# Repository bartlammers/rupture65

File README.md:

# Rupture65, a split 65% keyboard

## Left

[Project](./Left)  
[iBom](http://htmlpreview.github.io/?https://github.com/bartlammers/rupture65/blob/master/Left/bom/ibom.html)

## Right

[Project](./Right)  
[iBom](http://htmlpreview.github.io/?https://github.com/bartlammers/rupture65/blob/master/Right/bom/ibom.html)

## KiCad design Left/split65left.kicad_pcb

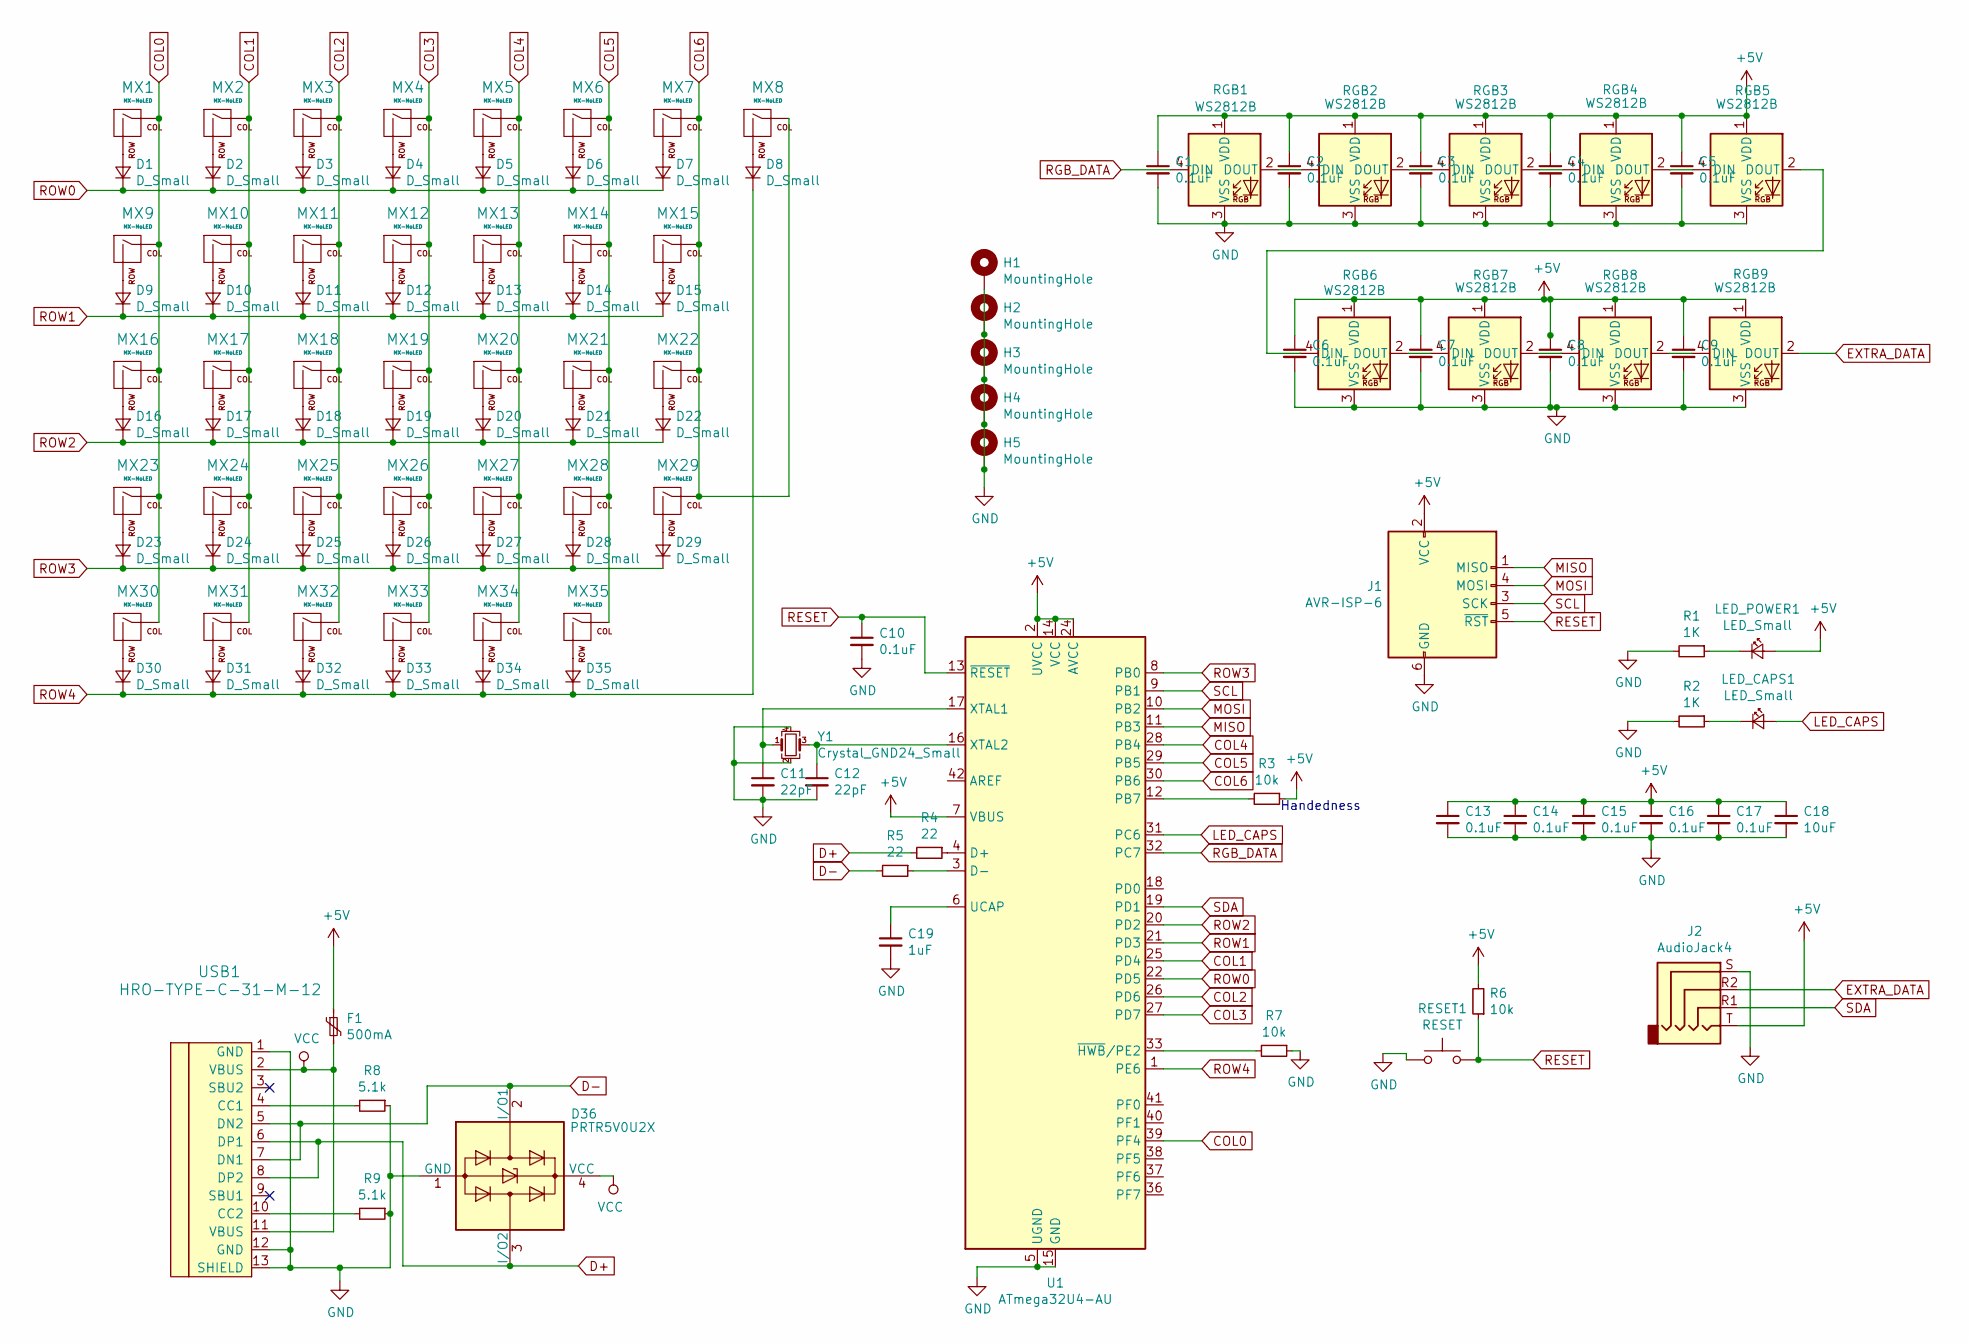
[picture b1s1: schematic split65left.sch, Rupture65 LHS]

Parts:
C1, C2, C3, C4, C5, C6, C7, C8, C9, C10, C13, C14, C15, C16, C17: 0.1uF; C_0805_2012Metric_Pad1.15x1.40mm_HandSolder
C11, C12: 22pF; C_0805_2012Metric_Pad1.15x1.40mm_HandSolder
C18: 10uF; C_0805_2012Metric_Pad1.15x1.40mm_HandSolder
C19: 1uF; C_0805_2012Metric_Pad1.15x1.40mm_HandSolder
D1, D2, D3, D4, D5, D6, D7, D8, D9, D10, D11, D12, D13, D14, D15, D16, D17, D18, D19, D20, D21, D22, D23, D24, D25, D26, D27, D28, D29, D30, D31, D32, D33, D34, D35: D_Small; D_SOD123_hand
D36: PRTR5V0U2X; SOT-143
F1: 500mA; Fuse_1206_3216Metric_Pad1.42x1.75mm_HandSolder
H1, H2, H3, H4, H5: MountingHole; MountingHole_2.2mm_M2_Pad_Via
J1: AVR-ISP-6; PinHeader_2x03_P2.54mm_Vertical
J2: AudioJack4; PJ-3200B-4A
LED_CAPS1: LED_Small; LED_0805_2012Metric
LED_POWER1: LED_Small; LED_0805_2012Metric
MX1, MX2, MX3, MX4, MX5, MX6, MX7, MX8, MX9, MX11, MX12, MX13, MX14, MX15, MX16, MX18, MX19, MX20, MX21, MX22, MX23, MX25, MX26, MX27, MX28, MX29, MX30: MX-NoLED; SW_Cherry_MX_1.00u_PCB
MX10: MX-NoLED; SW_Cherry_MX_1.50u_PCB
MX17: MX-NoLED; SW_Cherry_MX_1.75u_PCB
MX24: MX-NoLED; SW_Cherry_MX_2.25u_PCB
MX31, MX32, MX33, MX35: MX-NoLED; SW_Cherry_MX_1.25u_PCB
MX34: MX-NoLED; SW_Cherry_MX_2.25u_PCB_flippedstab
R1, R2: 1K; R_0805_2012Metric_Pad1.15x1.40mm_HandSolder
R3, R6, R7: 10k; R_0805_2012Metric_Pad1.15x1.40mm_HandSolder
R4, R5: 22; R_0805_2012Metric_Pad1.15x1.40mm_HandSolder
R8, R9: 5.1k; R_0805_2012Metric_Pad1.15x1.40mm_HandSolder
RESET1: RESET; SW_SPST_SKQG_WithStem
RGB1, RGB2, RGB3, RGB4, RGB5, RGB6, RGB7, RGB8, RGB9: WS2812B; LED_WS2812B_PLCC4_5.0x5.0mm_P3.2mm
U1: ATmega32U4-AU; TQFP-44_10x10mm_P0.8mm
USB1: HRO-TYPE-C-31-M-12; HRO-TYPE-C-31-M-12-HandSoldering
Y1: Crystal_GND24_Small; Crystal_SMD_3225-4Pin_3.2x2.5mm

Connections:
+5V: C1.1, C2.1, C3.1, C4.1, C5.1, C6.1, C7.1, C8.1, C9.1, C13.1, C14.1, C15.1, C16.1, C17.1, C18.1, F1.1, J1.2 (VCC), J2.T, LED_POWER1.2 (A), R3.1, R6.2, RGB1.1 (VDD), RGB2.1 (VDD), RGB3.1 (VDD), RGB4.1 (VDD), RGB5.1 (VDD), RGB6.1 (VDD), RGB7.1 (VDD), RGB8.1 (VDD), RGB9.1 (VDD), U1.2 (UVCC), U1.7 (VBUS), U1.14 (VCC), U1.24 (AVCC), U1.34 (VCC), U1.44 (AVCC)
COL0: MX1.1 (COL), MX9.1 (COL), MX16.1 (COL), MX23.1 (COL), MX30.1 (COL), U1.39 (PF4)
COL1: MX2.1 (COL), MX10.1 (COL), MX17.1 (COL), MX24.1 (COL), MX31.1 (COL), U1.25 (PD4)
COL2: MX3.1 (COL), MX11.1 (COL), MX18.1 (COL), MX25.1 (COL), MX32.1 (COL), U1.26 (PD6)
COL3: MX4.1 (COL), MX12.1 (COL), MX19.1 (COL), MX26.1 (COL), MX33.1 (COL), U1.27 (PD7)
COL4: MX5.1 (COL), MX13.1 (COL), MX20.1 (COL), MX27.1 (COL), MX34.1 (COL), U1.28 (PB4)
COL5: MX6.1 (COL), MX14.1 (COL), MX21.1 (COL), MX28.1 (COL), MX35.1 (COL), U1.29 (PB5)
COL6: MX7.1 (COL), MX8.1 (COL), MX15.1 (COL), MX22.1 (COL), MX29.1 (COL), U1.30 (PB6)
D+: D36.3 (I/O2), R4.2, USB1.6 (DP1), USB1.8 (DP2)
D-: D36.2 (I/O1), R5.2, USB1.5 (DN2), USB1.7 (DN1)
EXTRA_DATA: J2.R2, RGB9.2 (DOUT)
GND: C1.2, C2.2, C3.2, C4.2, C5.2, C6.2, C7.2, C8.2, C9.2, C10.2, C11.2, C12.2, C13.2, C14.2, C15.2, C16.2, C17.2, C18.2, C19.2, D36.1 (GND), H1.1, H2.1, H3.1, H4.1, H5.1, J1.6 (GND), J2.S, R1.2, R2.2, R7.1, R8.1, R9.1, RESET1.1, RGB1.3 (VSS), RGB2.3 (VSS), RGB3.3 (VSS), RGB4.3 (VSS), RGB5.3 (VSS), RGB6.3 (VSS), RGB7.3 (VSS), RGB8.3 (VSS), RGB9.3 (VSS), U1.5 (UGND), U1.15 (GND), U1.23 (GND), U1.35 (GND), U1.43 (GND), USB1.1 (GND), USB1.12 (GND), USB1.13 (SHIELD), Y1.2, Y1.4
LED_CAPS: LED_CAPS1.2 (A), U1.31 (PC6)
MISO: J1.1 (MISO), U1.11 (PB3)
MOSI: J1.4 (MOSI), U1.10 (PB2)
unnamed: C11.1, U1.17 (XTAL1), Y1.1
unnamed: C12.1, U1.16 (XTAL2), Y1.3
unnamed: C19.1, U1.6 (UCAP)
unnamed: D1.2 (A), MX1.2 (ROW)
unnamed: D2.2 (A), MX2.2 (ROW)
unnamed: D3.2 (A), MX3.2 (ROW)
unnamed: D4.2 (A), MX4.2 (ROW)
unnamed: D5.2 (A), MX5.2 (ROW)
unnamed: D6.2 (A), MX6.2 (ROW)
unnamed: D7.2 (A), MX7.2 (ROW)
unnamed: D8.2 (A), MX8.2 (ROW)
unnamed: D9.2 (A), MX9.2 (ROW)
unnamed: D10.2 (A), MX10.2 (ROW)
unnamed: D11.2 (A), MX11.2 (ROW)
unnamed: D12.2 (A), MX12.2 (ROW)
unnamed: D13.2 (A), MX13.2 (ROW)
unnamed: D14.2 (A), MX14.2 (ROW)
unnamed: D15.2 (A), MX15.2 (ROW)
unnamed: D16.2 (A), MX16.2 (ROW)
unnamed: D17.2 (A), MX17.2 (ROW)
unnamed: D18.2 (A), MX18.2 (ROW)
unnamed: D19.2 (A), MX19.2 (ROW)
unnamed: D20.2 (A), MX20.2 (ROW)
unnamed: D21.2 (A), MX21.2 (ROW)
unnamed: D22.2 (A), MX22.2 (ROW)
unnamed: D23.2 (A), MX23.2 (ROW)
unnamed: D24.2 (A), MX24.2 (ROW)
unnamed: D25.2 (A), MX25.2 (ROW)
unnamed: D26.2 (A), MX26.2 (ROW)
unnamed: D27.2 (A), MX27.2 (ROW)
unnamed: D28.2 (A), MX28.2 (ROW)
unnamed: D29.2 (A), MX29.2 (ROW)
unnamed: D30.2 (A), MX30.2 (ROW)
unnamed: D31.2 (A), MX31.2 (ROW)
unnamed: D32.2 (A), MX32.2 (ROW)
unnamed: D33.2 (A), MX33.2 (ROW)
unnamed: D34.2 (A), MX34.2 (ROW)
unnamed: D35.2 (A), MX35.2 (ROW)
unnamed: LED_CAPS1.1 (K), R2.1
unnamed: LED_POWER1.1 (K), R1.1
unnamed: R3.2, U1.12 (PB7)
unnamed: R4.1, U1.4 (D+)
unnamed: R5.1, U1.3 (D-)
unnamed: R7.2, U1.33 (~HWB~/PE2)
unnamed: R8.2, USB1.4 (CC1)
unnamed: R9.2, USB1.10 (CC2)
unnamed: RGB1.2 (DOUT), RGB2.4 (DIN)
unnamed: RGB2.2 (DOUT), RGB3.4 (DIN)
unnamed: RGB3.2 (DOUT), RGB4.4 (DIN)
unnamed: RGB4.2 (DOUT), RGB5.4 (DIN)
unnamed: RGB5.2 (DOUT), RGB6.4 (DIN)
unnamed: RGB6.2 (DOUT), RGB7.4 (DIN)
unnamed: RGB7.2 (DOUT), RGB8.4 (DIN)
unnamed: RGB8.2 (DOUT), RGB9.4 (DIN)
RESET: C10.1, J1.5 (~RST), R6.1, RESET1.2, U1.13 (~RESET)
RGB_DATA: RGB1.4 (DIN), U1.32 (PC7)
ROW0: D1.1 (K), D2.1 (K), D3.1 (K), D4.1 (K), D5.1 (K), D6.1 (K), D7.1 (K), U1.22 (PD5)
ROW1: D9.1 (K), D10.1 (K), D11.1 (K), D12.1 (K), D13.1 (K), D14.1 (K), D15.1 (K), U1.21 (PD3)
ROW2: D16.1 (K), D17.1 (K), D18.1 (K), D19.1 (K), D20.1 (K), D21.1 (K), D22.1 (K), U1.20 (PD2)
ROW3: D23.1 (K), D24.1 (K), D25.1 (K), D26.1 (K), D27.1 (K), D28.1 (K), D29.1 (K), U1.8 (PB0)
ROW4: D8.1 (K), D30.1 (K), D31.1 (K), D32.1 (K), D33.1 (K), D34.1 (K), D35.1 (K), U1.1 (PE6)
SCL: J1.3 (SCK), U1.9 (PB1)
SDA: J2.R1, U1.19 (PD1)
VCC: D36.4 (VCC), F1.2, USB1.2 (VBUS), USB1.11 (VBUS)

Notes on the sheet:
Handedness

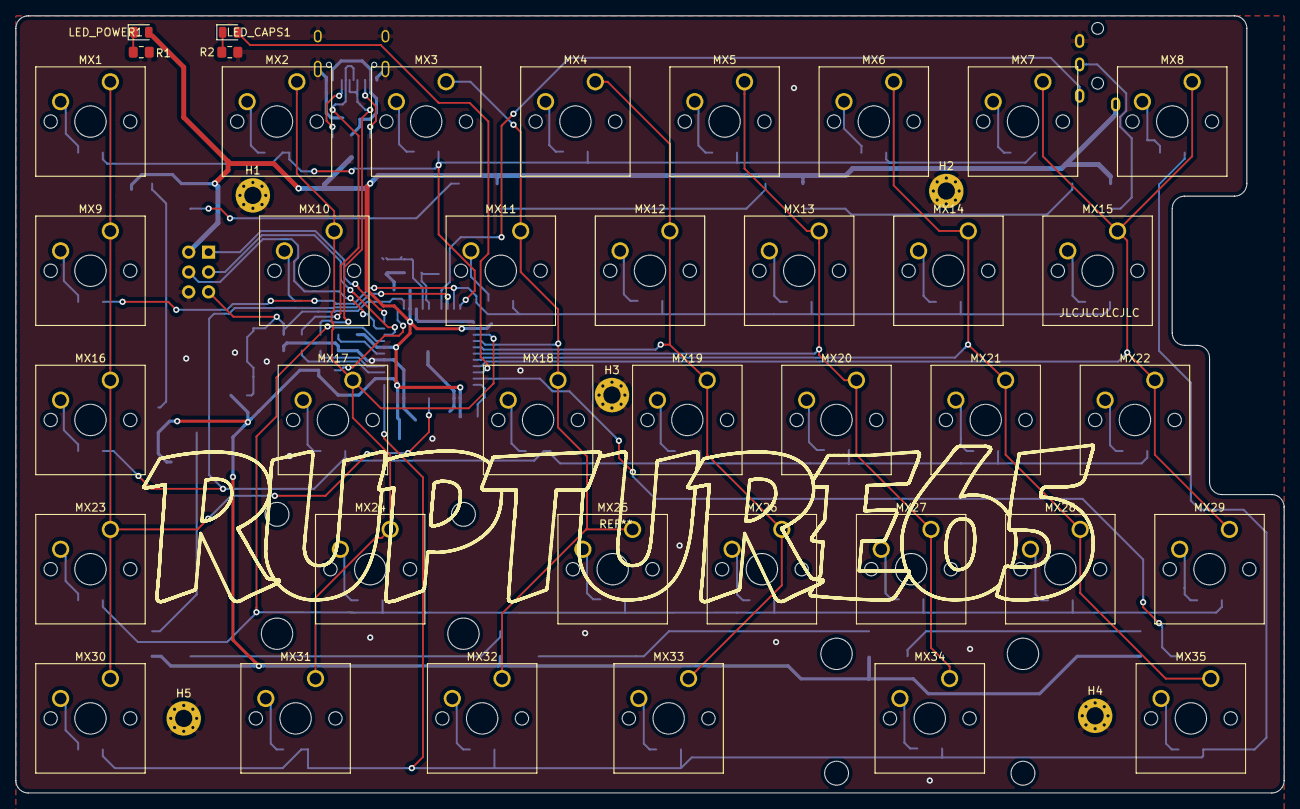
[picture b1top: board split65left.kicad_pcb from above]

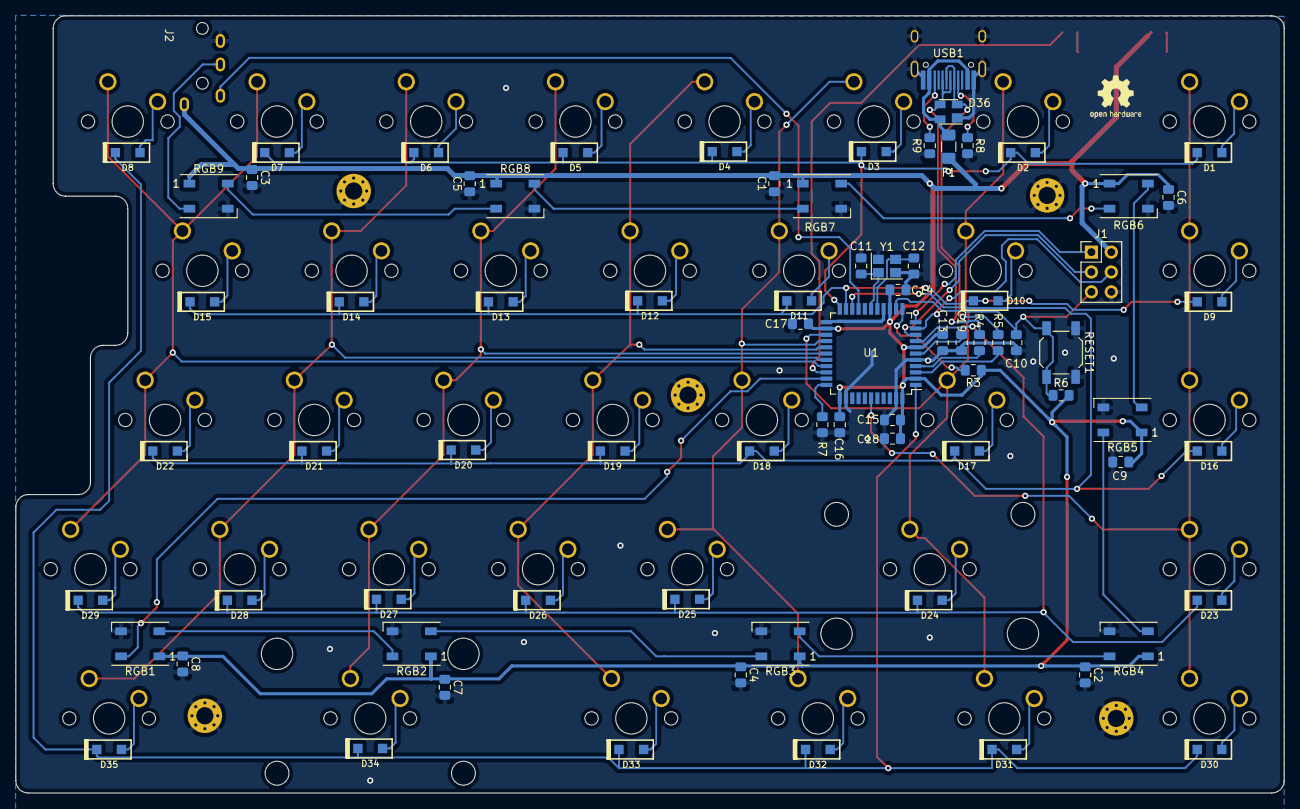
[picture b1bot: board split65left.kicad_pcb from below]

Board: 2 copper layers, 161.9 x 99.2 mm, 122 parts (78 on the bottom side), 79 nets.

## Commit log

2020-05-07 Add libraries
2020-09-19 Rev1 finished
2020-09-19 Add README.md
